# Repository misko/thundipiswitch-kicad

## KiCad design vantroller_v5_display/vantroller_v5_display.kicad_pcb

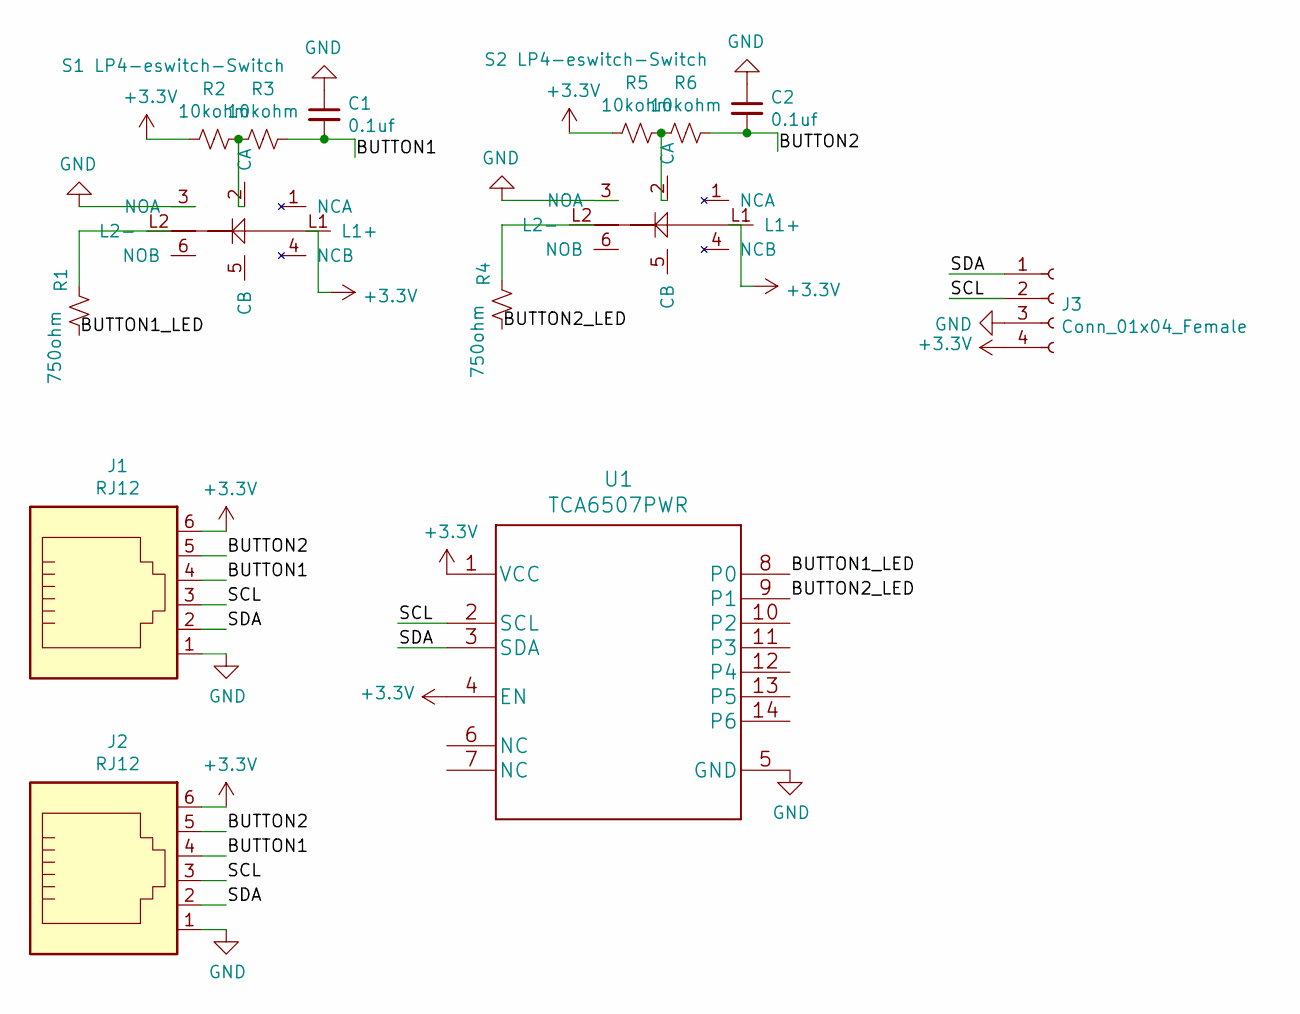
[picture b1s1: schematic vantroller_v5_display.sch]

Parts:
C1, C2: 0.1uf; C_0603_1608Metric
J1, J2: RJ12; 216446-1
J3: Conn_01x04_Female; PinHeader_1x04_P2.54mm_Vertical
R1, R4: 750ohm; R_1206_3216Metric
R2, R3, R5, R6: 10kohm; R_0402_1005Metric
S1, S2: LP4-eswitch-Switch; LP4-eswitch
U1: TCA6507PWR

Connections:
+3V3: J1.6, J2.6, J3.4, R2.2, R5.2, S1.L1 (L1+), S2.L1 (L1+), U1.1 (VCC), U1.4 (EN)
/BUTTON1: C1.2, J1.4, J2.4, R3.1
/BUTTON1_LED: R1.1, U1.8 (P0)
/BUTTON2: C2.2, J1.5, J2.5, R6.1
/BUTTON2_LED: R4.1, U1.9 (P1)
/SCL: J1.3, J2.3, J3.2, U1.2 (SCL)
/SDA: J1.2, J2.2, J3.1, U1.3 (SDA)
GND: C1.1, C2.1, J1.1, J2.1, J3.3, S1.3 (NOA), S2.3 (NOA), U1.5 (GND)
unnamed: R1.2, S1.L2 (L2-)
unnamed: R2.1, R3.2, S1.2 (CA)
unnamed: R4.2, S2.L2 (L2-)
unnamed: R5.1, R6.2, S2.2 (CA)

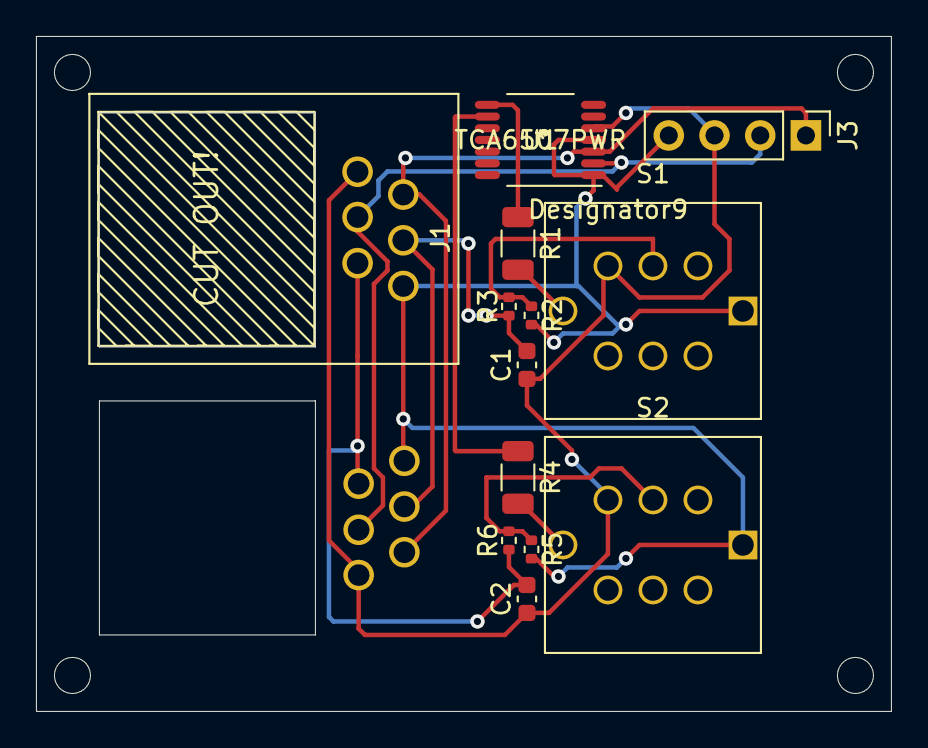
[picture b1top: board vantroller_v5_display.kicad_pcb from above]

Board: 2 copper layers, 47.5 x 37.5 mm, 14 parts (1 on the bottom side), 12 nets.

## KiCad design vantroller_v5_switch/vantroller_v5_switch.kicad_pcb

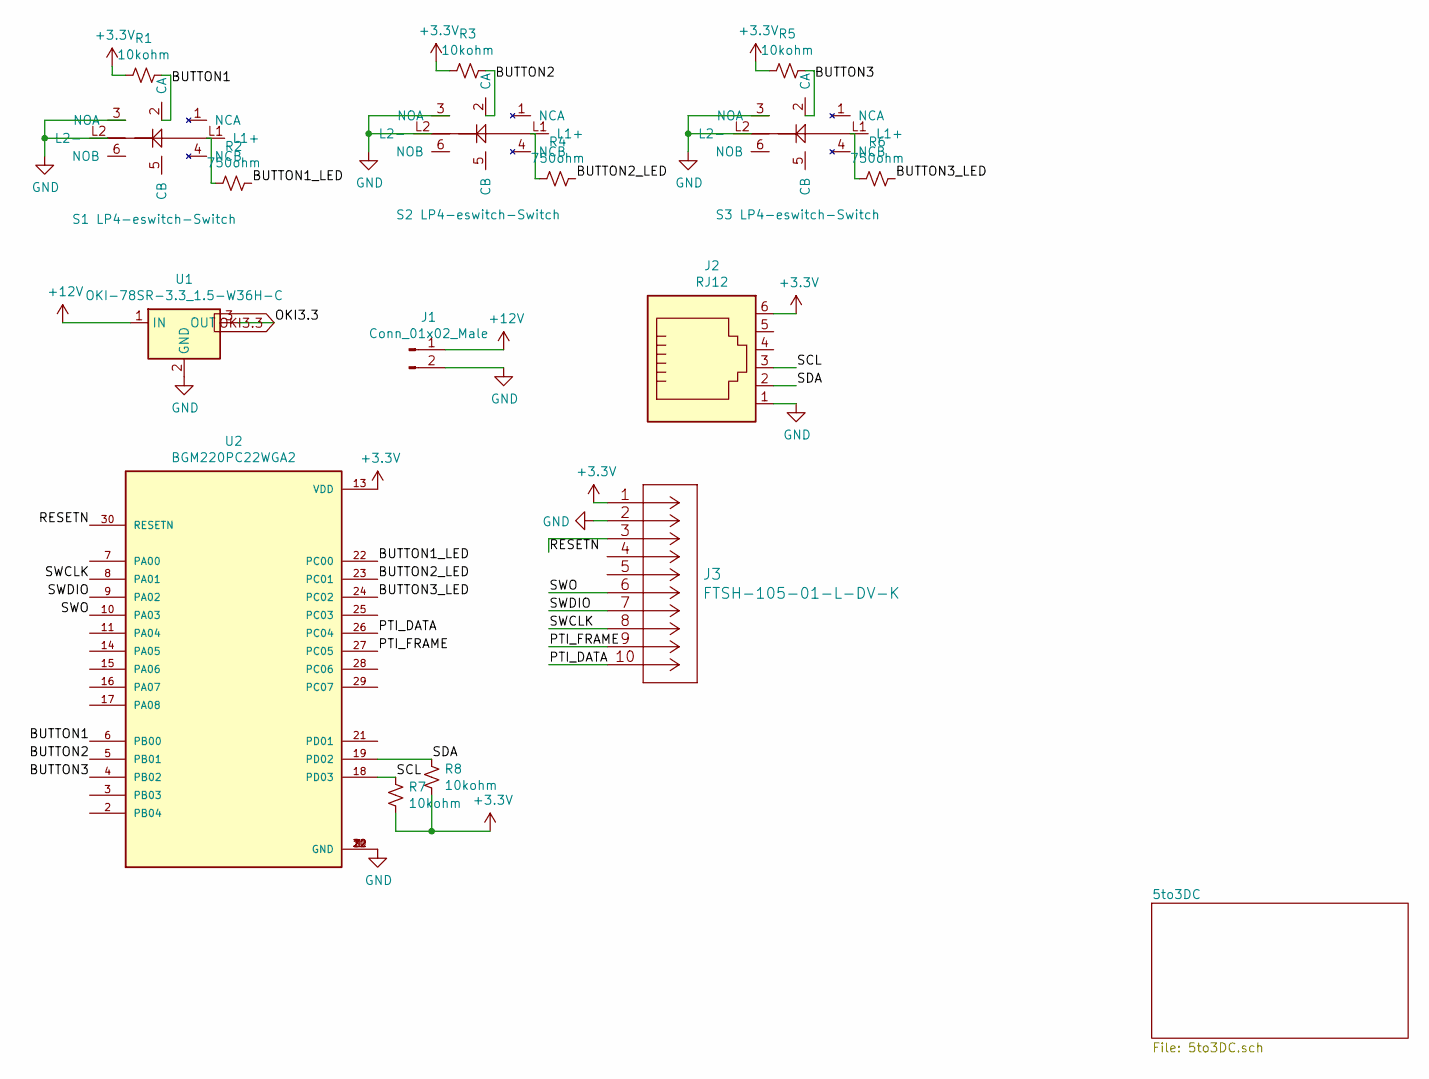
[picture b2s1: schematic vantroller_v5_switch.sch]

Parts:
J1: Conn_01x02_Male; TerminalBlock_Phoenix_PT-1,5-2-5.0-H_1x02_P5.00mm_Horizontal
J2: RJ12; 216446-1
J3: FTSH-105-01-L-DV-K
R1, R3, R5, R7, R8: 10kohm; R_0402_1005Metric
R2, R4, R6: 750ohm; R_1206_3216Metric
S1, S2, S3: LP4-eswitch-Switch; LP4-eswitch
U1: OKI-78SR-3.3_1.5-W36H-C; Converter_DCDC_muRata_OKI-78SR_Horizontal
U2: BGM220PC22WGA2; XCVR_BGM220PC22WGA2; PARTREV 1.0

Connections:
+3V3: J2.6, J3.1, R1.2, R3.2, R5.2, R7.2, R8.2, U2.13 (VDD); also elsewhere on the board
+12V: J1.1, U1.1 (IN)
/BUTTON1: R1.1, S1.2 (CA), U2.6 (PB00)
/BUTTON1_LED: R2.1, U2.22 (PC00)
/BUTTON2: R3.1, S2.2 (CA), U2.5 (PB01)
/BUTTON2_LED: R4.1, U2.23 (PC01)
/BUTTON3: R5.1, S3.2 (CA), U2.4 (PB02)
/BUTTON3_LED: R6.1, U2.24 (PC02)
/PTI_DATA: J3.10, U2.26 (PC04)
/PTI_FRAME: J3.9, U2.27 (PC05)
/RESETN: J3.3, U2.30 (RESETN)
/SCL: J2.3, R7.1, U2.18 (PD03)
/SDA: J2.2, R8.1, U2.19 (PD02)
/SWCLK: J3.8, U2.8 (PA01)
/SWDIO: J3.7, U2.9 (PA02)
/SWO: J3.6, U2.10 (PA03)
GND: J1.2, J2.1, J3.2, S1.3 (NOA), S1.L2 (L2-), S2.3 (NOA), S2.L2 (L2-), S3.3 (NOA), S3.L2 (L2-), U1.2 (GND), U2.1 (GND), U2.12 (GND), U2.20 (GND), U2.31 (GND); also elsewhere on the board
unnamed: R2.2, S1.L1 (L1+)
unnamed: R4.2, S2.L1 (L1+)
unnamed: R6.2, S3.L1 (L1+)
OKI3.3: U1.3 (OUT); also elsewhere on the board

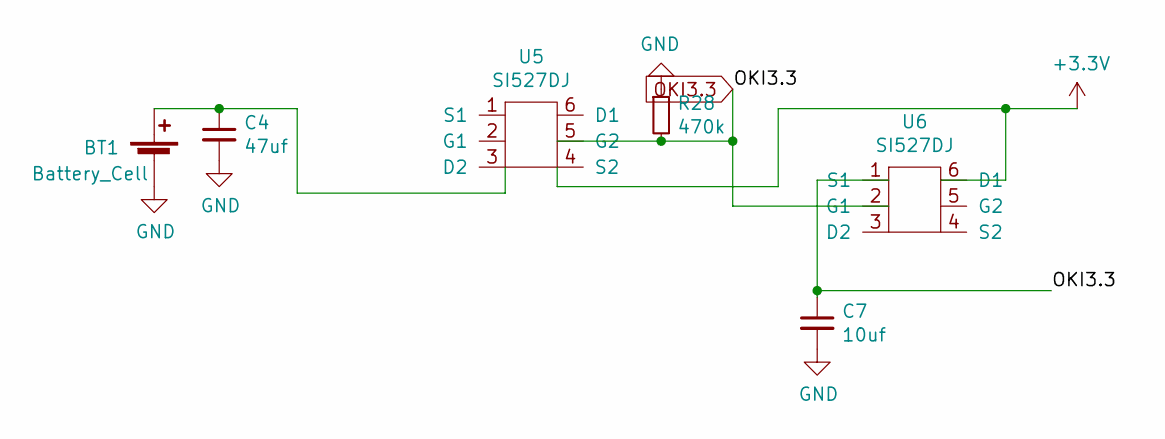
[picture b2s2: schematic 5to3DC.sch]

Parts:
BT1: Battery_Cell; BatteryHolder_Keystone_3034_1x20mm
C4: 47uf; C_1206_3216Metric
C7: 10uf; C_1210_3225Metric
R28: 470k; R_0603_1608Metric
U5, U6: SI527DJ; Vishay_PowerPAK_SC70-6L_Dual

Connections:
+3V3: U5.4 (S2), U6.6 (D1); also elsewhere on the board
GND: BT1.2 (-), C4.2, C7.2, R28.1; also elsewhere on the board
unnamed: BT1.1 (+), C4.1, U5.3 (D2)
OKI3.3: C7.1, R28.2, U5.5 (G2), U6.1 (S1), U6.2 (G1); also elsewhere on the board

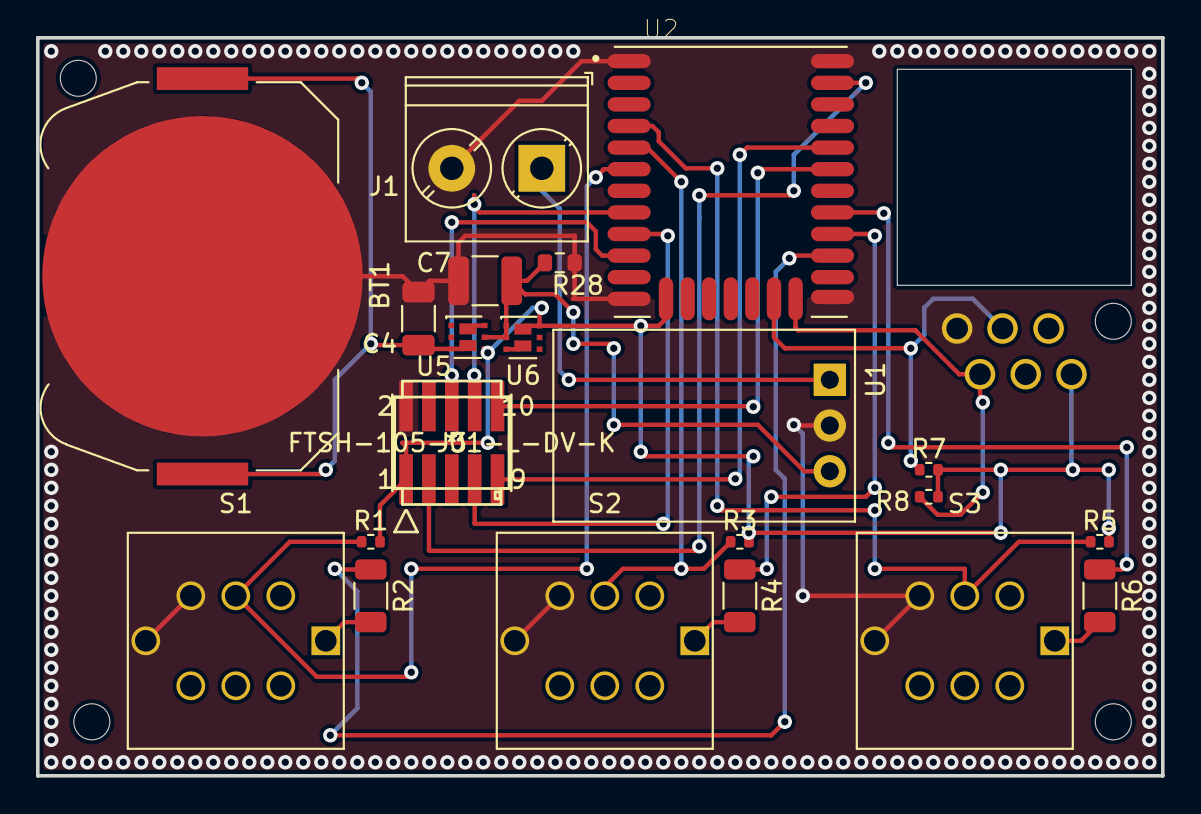
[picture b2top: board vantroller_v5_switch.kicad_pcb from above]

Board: 2 copper layers, 62.5 x 41.0 mm, 22 parts (1 on the bottom side), 22 nets.

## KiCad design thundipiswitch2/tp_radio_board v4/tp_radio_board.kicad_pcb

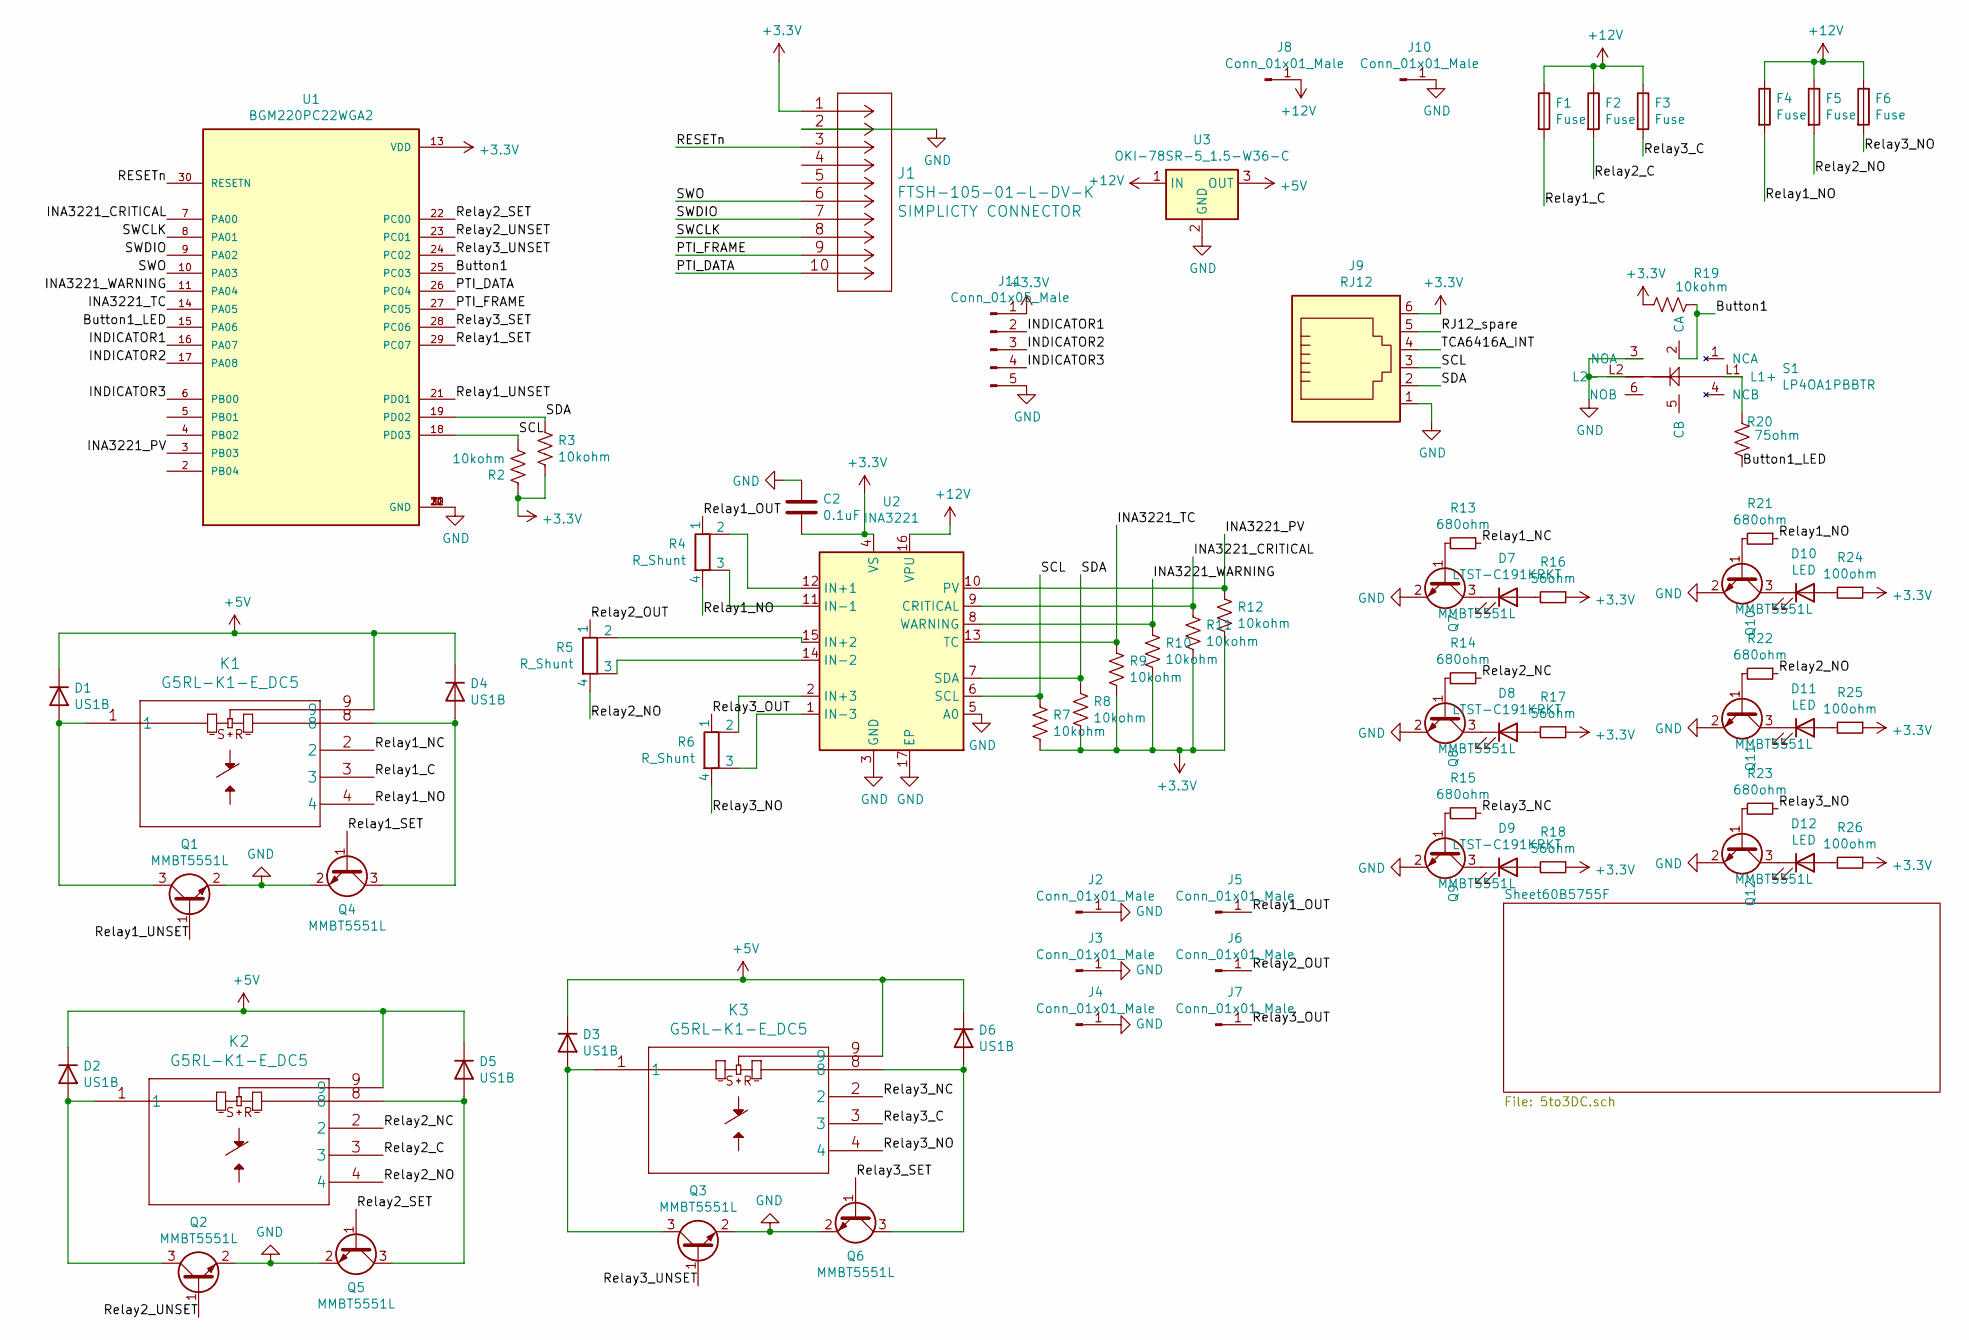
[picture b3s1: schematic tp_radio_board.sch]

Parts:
C2: 0.1uF; C_0402_1005Metric
D1, D2, D3, D4, D5, D6: US1B; D_SMA
D7, D8, D9: LTST-C191KRKT; LED_0603_1608Metric_Castellated
D10, D11, D12: LED; LED_0603_1608Metric_Castellated
F1, F2, F3, F4, F5, F6: Fuse; Fuseholder_Blade_Mini_Keystone_3568
J1: FTSH-105-01-L-DV-K
J2, J3, J4, J5, J6, J7: Conn_01x01_Male; Wuerth_REDCUBE-THR_WP-THRSH_74651175_THR
J8, J10: Conn_01x01_Male; Wuerth_REDCUBE-THR_WP-THRSH_74651194_THR
J9: RJ12; 216446-1
J11: Conn_01x05_Male; PinHeader_1x05_P2.54mm_Vertical
K1, K2, K3: G5RL-K1-E_DC5; G5RL-K1-E-DC5
Q1, Q2, Q3, Q4, Q5, Q6, Q7, Q8, Q9, Q10, Q11, Q12: MMBT5551L; SOT-23
R2, R3, R7, R8, R9, R10, R11, R12, R19: 10kohm; R_0402_1005Metric
R4, R5, R6: R_Shunt; R_Shunt_Ohmite_LVK25
R13, R14, R15, R21, R22, R23: 680ohm; R_0603_1608Metric
R16, R17, R18: 56ohm; R_1206_3216Metric
R20: 75ohm; R_1206_3216Metric
R24, R25, R26: 100ohm; R_1206_3216Metric
S1: LP4OA1PBBTR‎; LP4-eswitch
U1: BGM220PC22WGA2; XCVR_BGM220PC22WGA2; PARTREV 1.0
U2: INA3221; Texas_RGV_S-PVQFN-N16_EP2.1x2.1mm
U3: OKI-78SR-5_1.5-W36-C; Converter_DCDC_muRata_OKI-78SR_Vertical

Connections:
+3V3: C2.2, J1.1, J9.6, J11.1, R2.2, R3.1, R7.1, R8.1, R9.1, R10.1, R11.1, R12.1, R16.1, R17.1, R18.1, R19.1, R24.1, R25.1, R26.1, U1.13 (VDD), U2.4 (VS); also elsewhere on the board
+5V: D1.1 (K), D2.1 (K), D3.1 (K), D4.1 (K), D5.1 (K), D6.1 (K), K1.9, K2.9, K3.9, U3.3 (OUT); also elsewhere on the board
+12V: F1.1, F2.1, F3.1, F4.1, F5.1, F6.1, J8.1, U2.16 (VPU), U3.1 (IN)
/Button1: R19.2, S1.2 (CA), U1.25 (PC03)
/Button1_LED: R20.2, U1.15 (PA06)
/INA3221_CRITICAL: R11.2, U1.7 (PA00), U2.9 (CRITICAL)
/INA3221_PV: R12.2, U1.3 (PB03), U2.10 (PV)
/INA3221_TC: R9.2, U1.14 (PA05), U2.13 (TC)
/INA3221_WARNING: R10.2, U1.11 (PA04), U2.8 (WARNING)
/INDICATOR1: J11.2, U1.16 (PA07)
/INDICATOR2: J11.3, U1.17 (PA08)
/INDICATOR3: J11.4, U1.6 (PB00)
/PTI_DATA: J1.10, U1.26 (PC04)
/PTI_FRAME: J1.9, U1.27 (PC05)
/RESETn: J1.3, U1.30 (RESETN)
/RJ12_spare: J9.5
/Relay1_C: F1.2, K1.3
/Relay1_NC: K1.2, R13.1
/Relay1_NO: F4.2, K1.4, R4.4, R21.1
/Relay1_OUT: J5.1, R4.1
/Relay1_SET: Q4.1 (B), U1.29 (PC07)
/Relay1_UNSET: Q1.1 (B), U1.21 (PD01)
/Relay2_C: F2.2, K2.3
/Relay2_NC: K2.2, R14.1
/Relay2_NO: F5.2, K2.4, R5.4, R22.1
/Relay2_OUT: J6.1, R5.1
/Relay2_SET: Q5.1 (B), U1.22 (PC00)
/Relay2_UNSET: Q2.1 (B), U1.23 (PC01)
/Relay3_C: F3.2, K3.3
/Relay3_NC: K3.2, R15.1
/Relay3_NO: F6.2, K3.4, R6.4, R23.1
/Relay3_OUT: J7.1, R6.1
/Relay3_SET: Q6.1 (B), U1.28 (PC06)
/Relay3_UNSET: Q3.1 (B), U1.24 (PC02)
/SCL: J9.3, R2.1, R7.2, U1.18 (PD03), U2.6 (SCL)
/SDA: J9.2, R3.2, R8.2, U1.19 (PD02), U2.7 (SDA)
/SWCLK: J1.8, U1.8 (PA01)
/SWDIO: J1.7, U1.9 (PA02)
/SWO: J1.6, U1.10 (PA03)
/TCA6416A_INT: J9.4
GND: C2.1, J1.2, J2.1, J3.1, J4.1, J9.1, J10.1, J11.5, Q1.2 (E), Q2.2 (E), Q3.2 (E), Q4.2 (E), Q5.2 (E), Q6.2 (E), Q7.2 (E), Q8.2 (E), Q9.2 (E), Q10.2 (E), Q11.2 (E), Q12.2 (E), S1.3 (NOA), S1.L2 (L2-), U1.1 (GND), U1.12 (GND), U1.20 (GND), U1.31 (GND), U2.3 (GND), U2.5 (A0), U2.17 (EP), U3.2 (GND); also elsewhere on the board
unnamed: D1.2 (A), K1.1, Q1.3 (C)
unnamed: D2.2 (A), K2.1, Q2.3 (C)
unnamed: D3.2 (A), K3.1, Q3.3 (C)
unnamed: D4.2 (A), K1.8, Q4.3 (C)
unnamed: D5.2 (A), K2.8, Q5.3 (C)
unnamed: D6.2 (A), K3.8, Q6.3 (C)
unnamed: D7.1 (K), Q7.3 (C)
unnamed: D7.2 (A), R16.2
unnamed: D8.1 (K), Q8.3 (C)
unnamed: D8.2 (A), R17.2
unnamed: D9.1 (K), Q9.3 (C)
unnamed: D9.2 (A), R18.2
unnamed: D10.1 (K), Q10.3 (C)
unnamed: D10.2 (A), R24.2
unnamed: D11.1 (K), Q11.3 (C)
unnamed: D11.2 (A), R25.2
unnamed: D12.1 (K), Q12.3 (C)
unnamed: D12.2 (A), R26.2
unnamed: Q7.1 (B), R13.2
unnamed: Q8.1 (B), R14.2
unnamed: Q9.1 (B), R15.2
unnamed: Q10.1 (B), R21.2
unnamed: Q11.1 (B), R22.2
unnamed: Q12.1 (B), R23.2
unnamed: R4.2, U2.12 (IN+1)
unnamed: R4.3, U2.11 (IN-1)
unnamed: R5.2, U2.15 (IN+2)
unnamed: R5.3, U2.14 (IN-2)
unnamed: R6.2, U2.2 (IN+3)
unnamed: R6.3, U2.1 (IN-3)
unnamed: R20.1, S1.L1 (L1+)

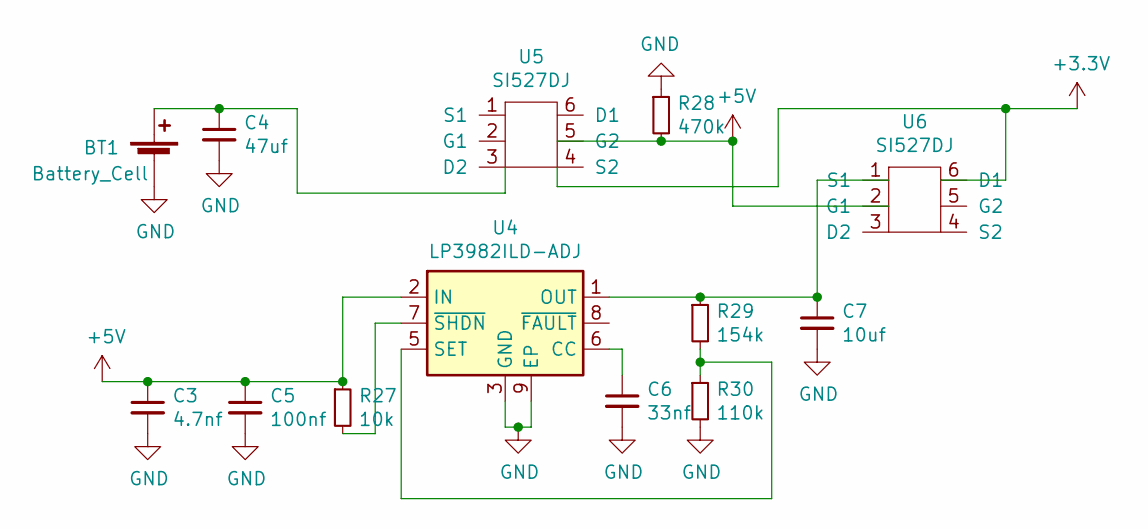
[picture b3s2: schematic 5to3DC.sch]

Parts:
BT1: Battery_Cell; BatteryHolder_Keystone_3034_1x20mm
C3: 4.7nf; C_0402_1005Metric
C4: 47uf; C_1206_3216Metric
C5: 100nf; C_0603_1608Metric
C6: 33nf; C_0603_1608Metric
C7: 10uf; C_1210_3225Metric
R27: 10k; R_0402_1005Metric
R28: 470k; R_0603_1608Metric
R29: 154k; R_0603_1608Metric
R30: 110k; R_0603_1608Metric
U4: LP3982ILD-ADJ; WSON-8-1EP_3x2.5mm_P0.5mm_EP1.2x1.5mm_PullBack_ThermalVias
U5, U6: SI527DJ; Vishay_PowerPAK_SC70-6L_Dual

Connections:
+3V3: U5.4 (S2), U6.6 (D1); also elsewhere on the board
+5V: C3.1, C5.1, R27.1, R28.2, U4.2 (IN), U5.5 (G2), U6.2 (G1); also elsewhere on the board
GND: BT1.2 (-), C3.2, C4.2, C5.2, C6.2, C7.2, R28.1, R30.2, U4.3 (GND), U4.9 (EP); also elsewhere on the board
unnamed: BT1.1 (+), C4.1, U5.3 (D2)
unnamed: C6.1, U4.6 (CC)
unnamed: C7.1, R29.1, U4.1 (OUT), U4.4 (OUT), U6.1 (S1)
unnamed: R27.2, U4.7 (~SHDN)
unnamed: R29.2, R30.1, U4.5 (SET)

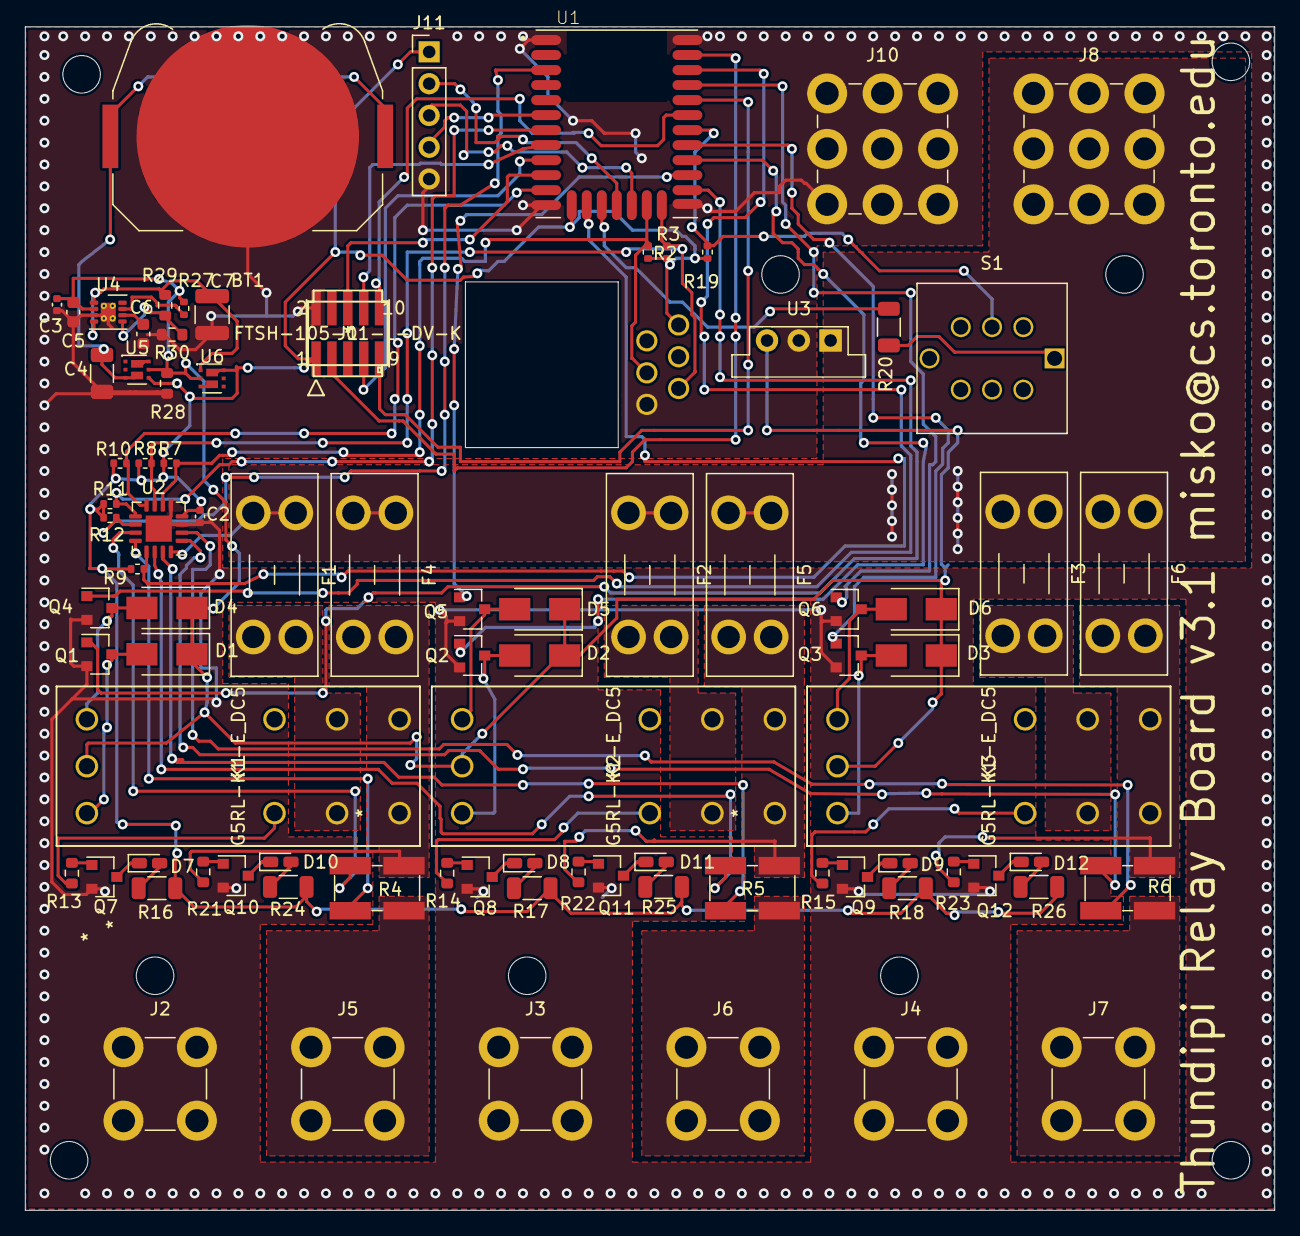
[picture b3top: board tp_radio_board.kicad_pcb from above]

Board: 2 copper layers, 99.9 x 94.6 mm, 87 parts (1 on the bottom side), 75 nets.

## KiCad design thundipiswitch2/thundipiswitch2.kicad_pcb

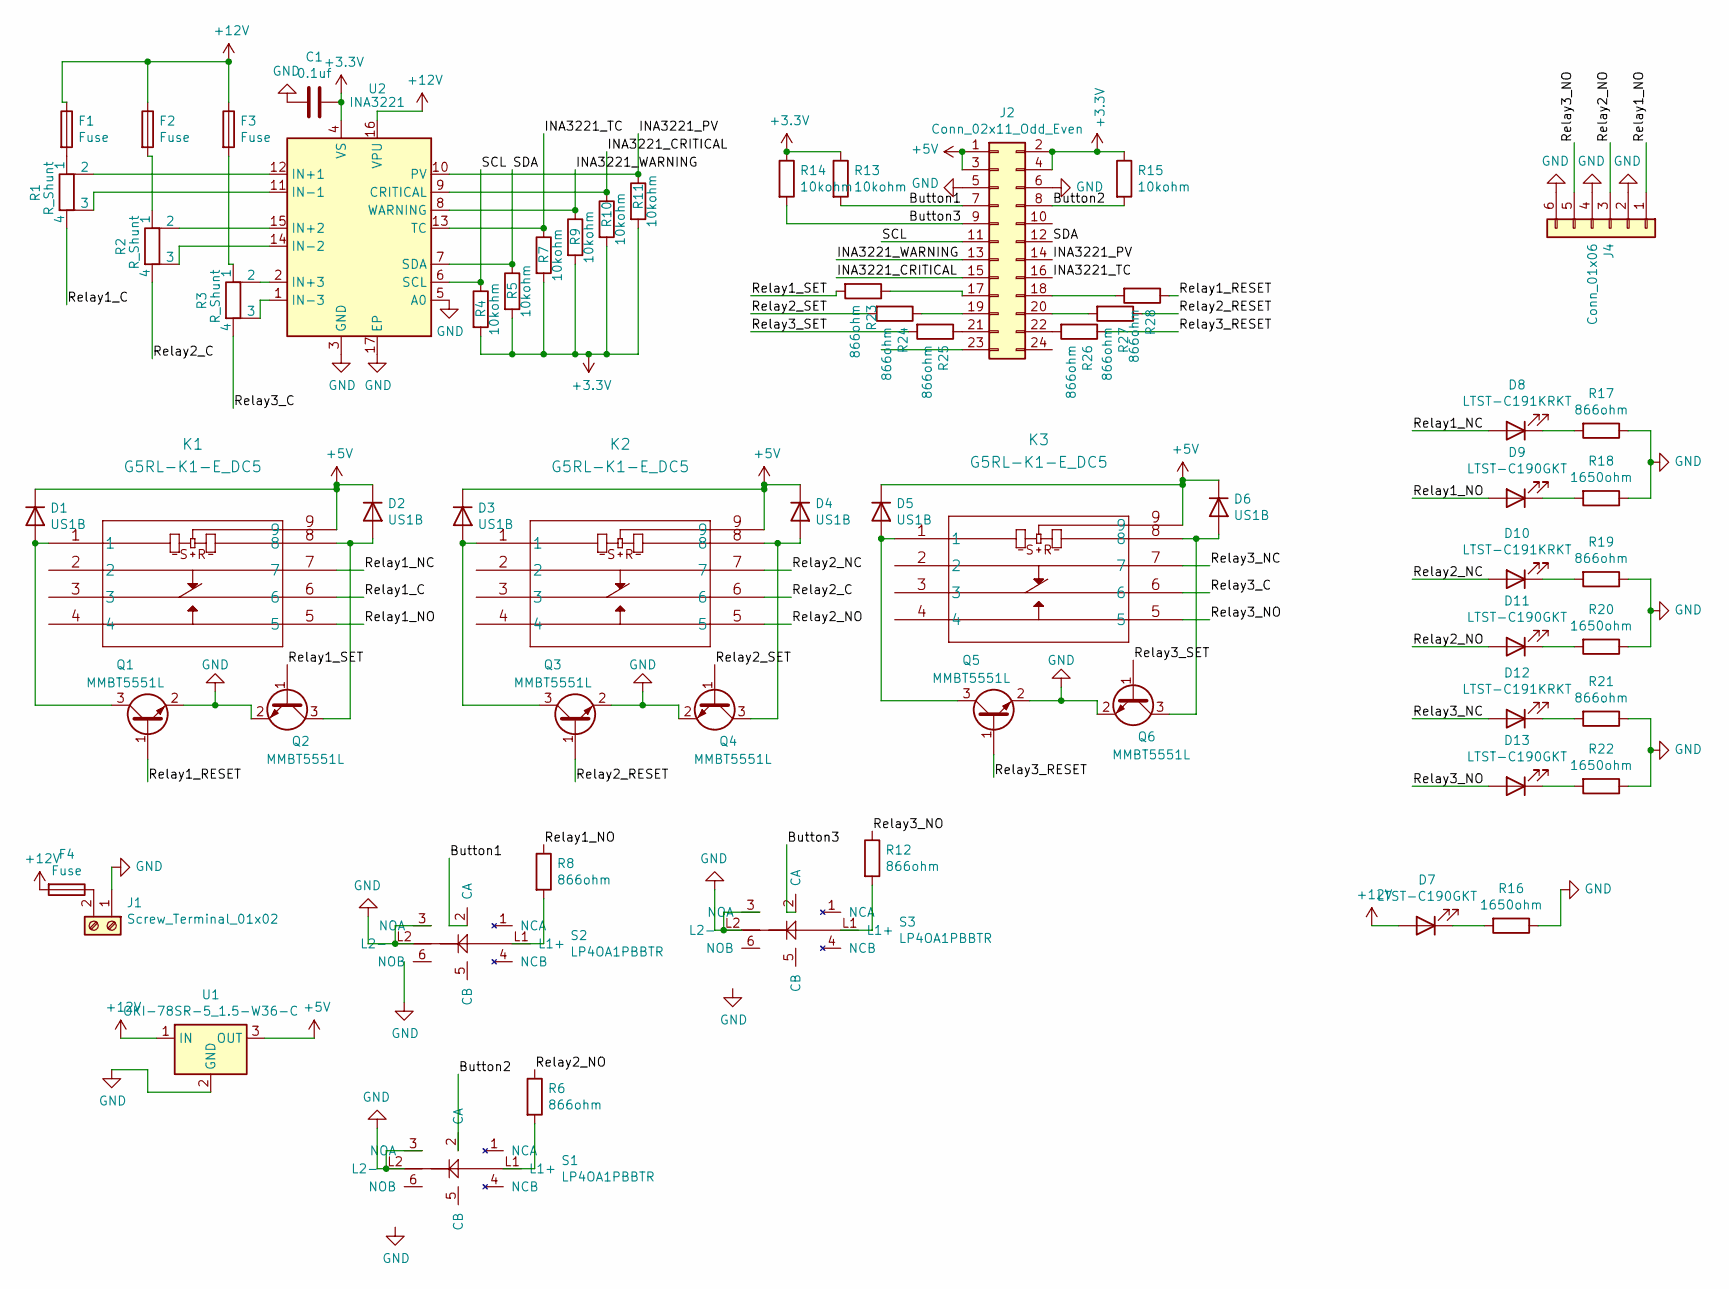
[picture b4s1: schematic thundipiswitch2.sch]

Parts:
C1: 0.1uf; C_0402_1005Metric
D1, D2, D3, D4, D5, D6: US1B; D_SMA
D7, D9, D11, D13: LTST-C190GKT; LED_0603_1608Metric_Castellated
D8, D10, D12: LTST-C191KRKT‎; LED_0603_1608Metric_Castellated
F1, F2, F3, F4: Fuse; Fuseholder_Blade_Mini_Keystone_3568
J1: Screw_Terminal_01x02; 1714971
J2: Conn_02x11_Odd_Even; PinHeader_2x12_P2.54mm_Vertical
J4: Conn_01x06; 1715190
K1, K2, K3: G5RL-K1-E_DC5; G5RL-K1-E-DC5
Q1, Q2, Q3, Q4, Q5, Q6: MMBT5551L; SOT-23
R1, R2, R3: R_Shunt; R_Shunt_Ohmite_LVK25
R4, R5, R7, R9, R10, R11, R13, R14, R15: 10kohm; R_0402_1005Metric
R6, R8, R12, R17, R19, R21, R23, R24, R25, R26, R27, R28: 866ohm; R_1206_3216Metric
R16, R18, R20, R22: 1650ohm; R_1206_3216Metric
S1, S2, S3: LP4OA1PBBTR‎; LP4-eswitch
U1: OKI-78SR-5_1.5-W36-C; Converter_DCDC_muRata_OKI-78SR_Vertical
U2: INA3221; Texas_RGV_S-PVQFN-N16_EP2.1x2.1mm

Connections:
+3V3: C1.2, J2.2, J2.4, R4.2, R5.2, R7.2, R9.2, R10.2, R11.2, R13.1, R14.1, R15.1, U2.4 (VS)
+5V: D1.1 (K), D2.1 (K), D3.1 (K), D4.1 (K), D5.1 (K), D6.1 (K), J2.1, J2.3, K1.9, K2.9, K3.9, U1.3 (OUT)
+12V: D7.2 (A), F1.1, F2.1, F3.1, F4.2, U1.1 (IN), U2.16 (VPU)
/Button1: J2.7, R13.2, S2.2 (CA)
/Button2: J2.8, R15.2, S1.2 (CA)
/Button3: J2.9, R14.2, S3.2 (CA)
/INA3221_CRITICAL: J2.15, R10.1, U2.9 (CRITICAL)
/INA3221_PV: J2.14, R11.1, U2.10 (PV)
/INA3221_TC: J2.16, R7.1, U2.13 (TC)
/INA3221_WARNING: J2.13, R9.1, U2.8 (WARNING)
/Relay1_C: K1.6, R1.4
/Relay1_NC: D8.2 (A), K1.7
/Relay1_NO: D9.2 (A), J4.1, K1.5, R8.1
/Relay1_RESET: Q1.1 (B), R28.1
/Relay1_SET: Q2.1 (B), R23.2
/Relay2_C: K2.6, R2.4
/Relay2_NC: D10.2 (A), K2.7
/Relay2_NO: D11.2 (A), J4.3, K2.5, R6.1
/Relay2_RESET: Q3.1 (B), R27.1
/Relay2_SET: Q4.1 (B), R24.2
/Relay3_C: K3.6, R3.4
/Relay3_NC: D12.2 (A), K3.7
/Relay3_NO: D13.2 (A), J4.5, K3.5, R12.1
/Relay3_RESET: Q5.1 (B), R26.1
/Relay3_SET: Q6.1 (B), R25.2
/SCL: J2.11, R4.1, U2.6 (SCL)
/SDA: J2.12, R5.1, U2.7 (SDA)
GND: C1.1, J1.1, J2.5, J2.6, J4.2, J4.4, J4.6, Q1.2 (E), Q2.2 (E), Q3.2 (E), Q4.2 (E), Q5.2 (E), Q6.2 (E), R16.1, R17.1, R18.1, R19.1, R20.1, R21.1, R22.1, S1.3 (NOA), S1.L2 (L2-), S2.3 (NOA), S2.L2 (L2-), S3.3 (NOA), S3.L2 (L2-), U1.2 (GND), U2.3 (GND), U2.5 (A0), U2.17 (EP)
unnamed: D1.2 (A), K1.1, Q1.3 (C)
unnamed: D2.2 (A), K1.8, Q2.3 (C)
unnamed: D3.2 (A), K2.1, Q3.3 (C)
unnamed: D4.2 (A), K2.8, Q4.3 (C)
unnamed: D5.2 (A), K3.1, Q5.3 (C)
unnamed: D6.2 (A), K3.8, Q6.3 (C)
unnamed: D7.1 (K), R16.2
unnamed: D8.1 (K), R17.2
unnamed: D9.1 (K), R18.2
unnamed: D10.1 (K), R19.2
unnamed: D11.1 (K), R20.2
unnamed: D12.1 (K), R21.2
unnamed: D13.1 (K), R22.2
unnamed: F1.2, R1.1
unnamed: F2.2, R2.1
unnamed: F3.2, R3.1
unnamed: F4.1, J1.2
unnamed: J2.17, R23.1
unnamed: J2.18, R28.2
unnamed: J2.19, R24.1
unnamed: J2.20, R27.2
unnamed: J2.21, R25.1
unnamed: J2.22, R26.2
unnamed: R1.2, U2.12 (IN+1)
unnamed: R1.3, U2.11 (IN-1)
unnamed: R2.2, U2.15 (IN+2)
unnamed: R2.3, U2.14 (IN-2)
unnamed: R3.2, U2.2 (IN+3)
unnamed: R3.3, U2.1 (IN-3)
unnamed: R6.2, S1.L1 (L1+)
unnamed: R8.2, S2.L1 (L1+)
unnamed: R12.2, S3.L1 (L1+)

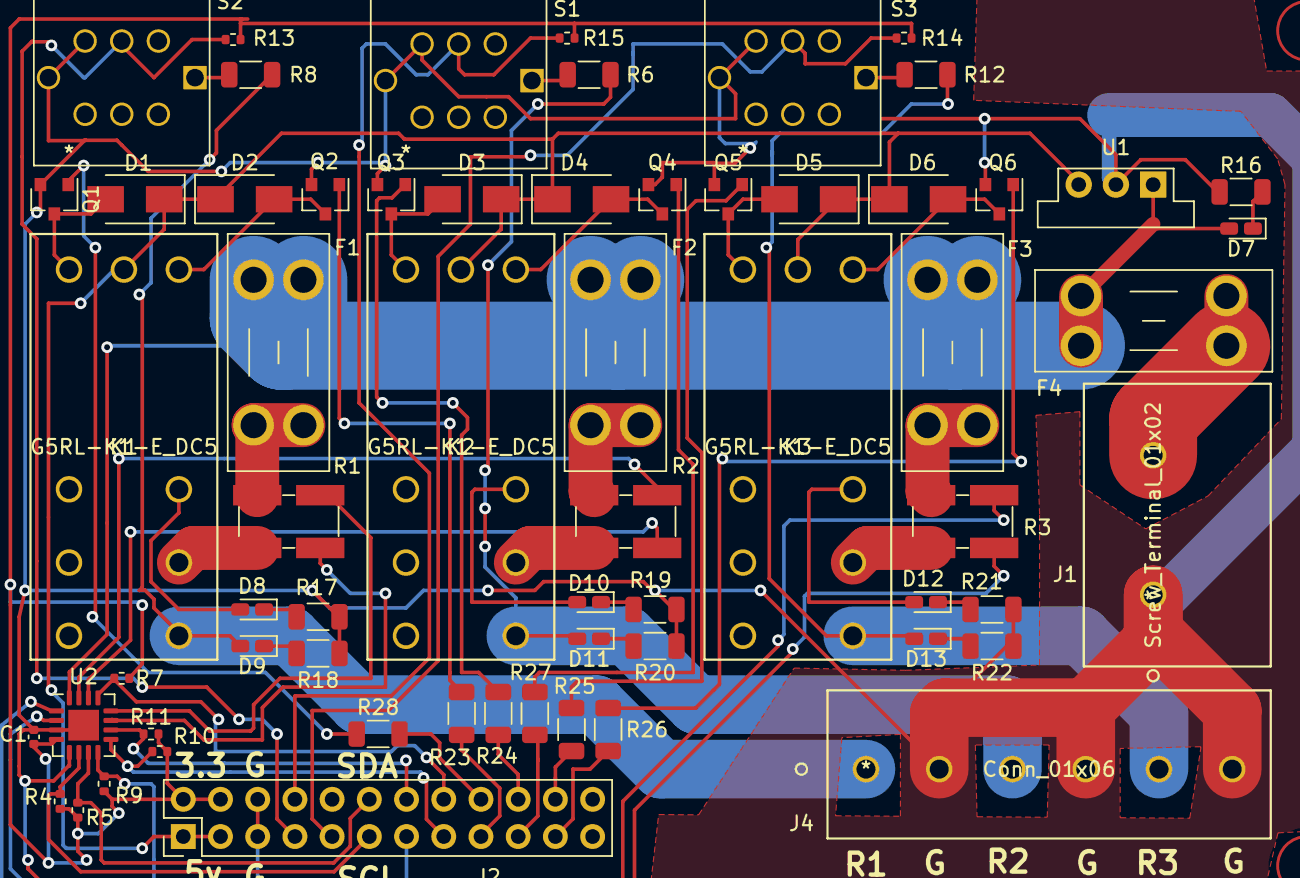
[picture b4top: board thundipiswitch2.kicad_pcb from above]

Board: 2 copper layers, 63 parts (0 on the bottom side), 60 nets.

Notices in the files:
parts and their libraries:
Copyright 2016 Accelerated Designs. All rights reserved.
Copyright 2021 Accelerated Designs. All rights reserved.
